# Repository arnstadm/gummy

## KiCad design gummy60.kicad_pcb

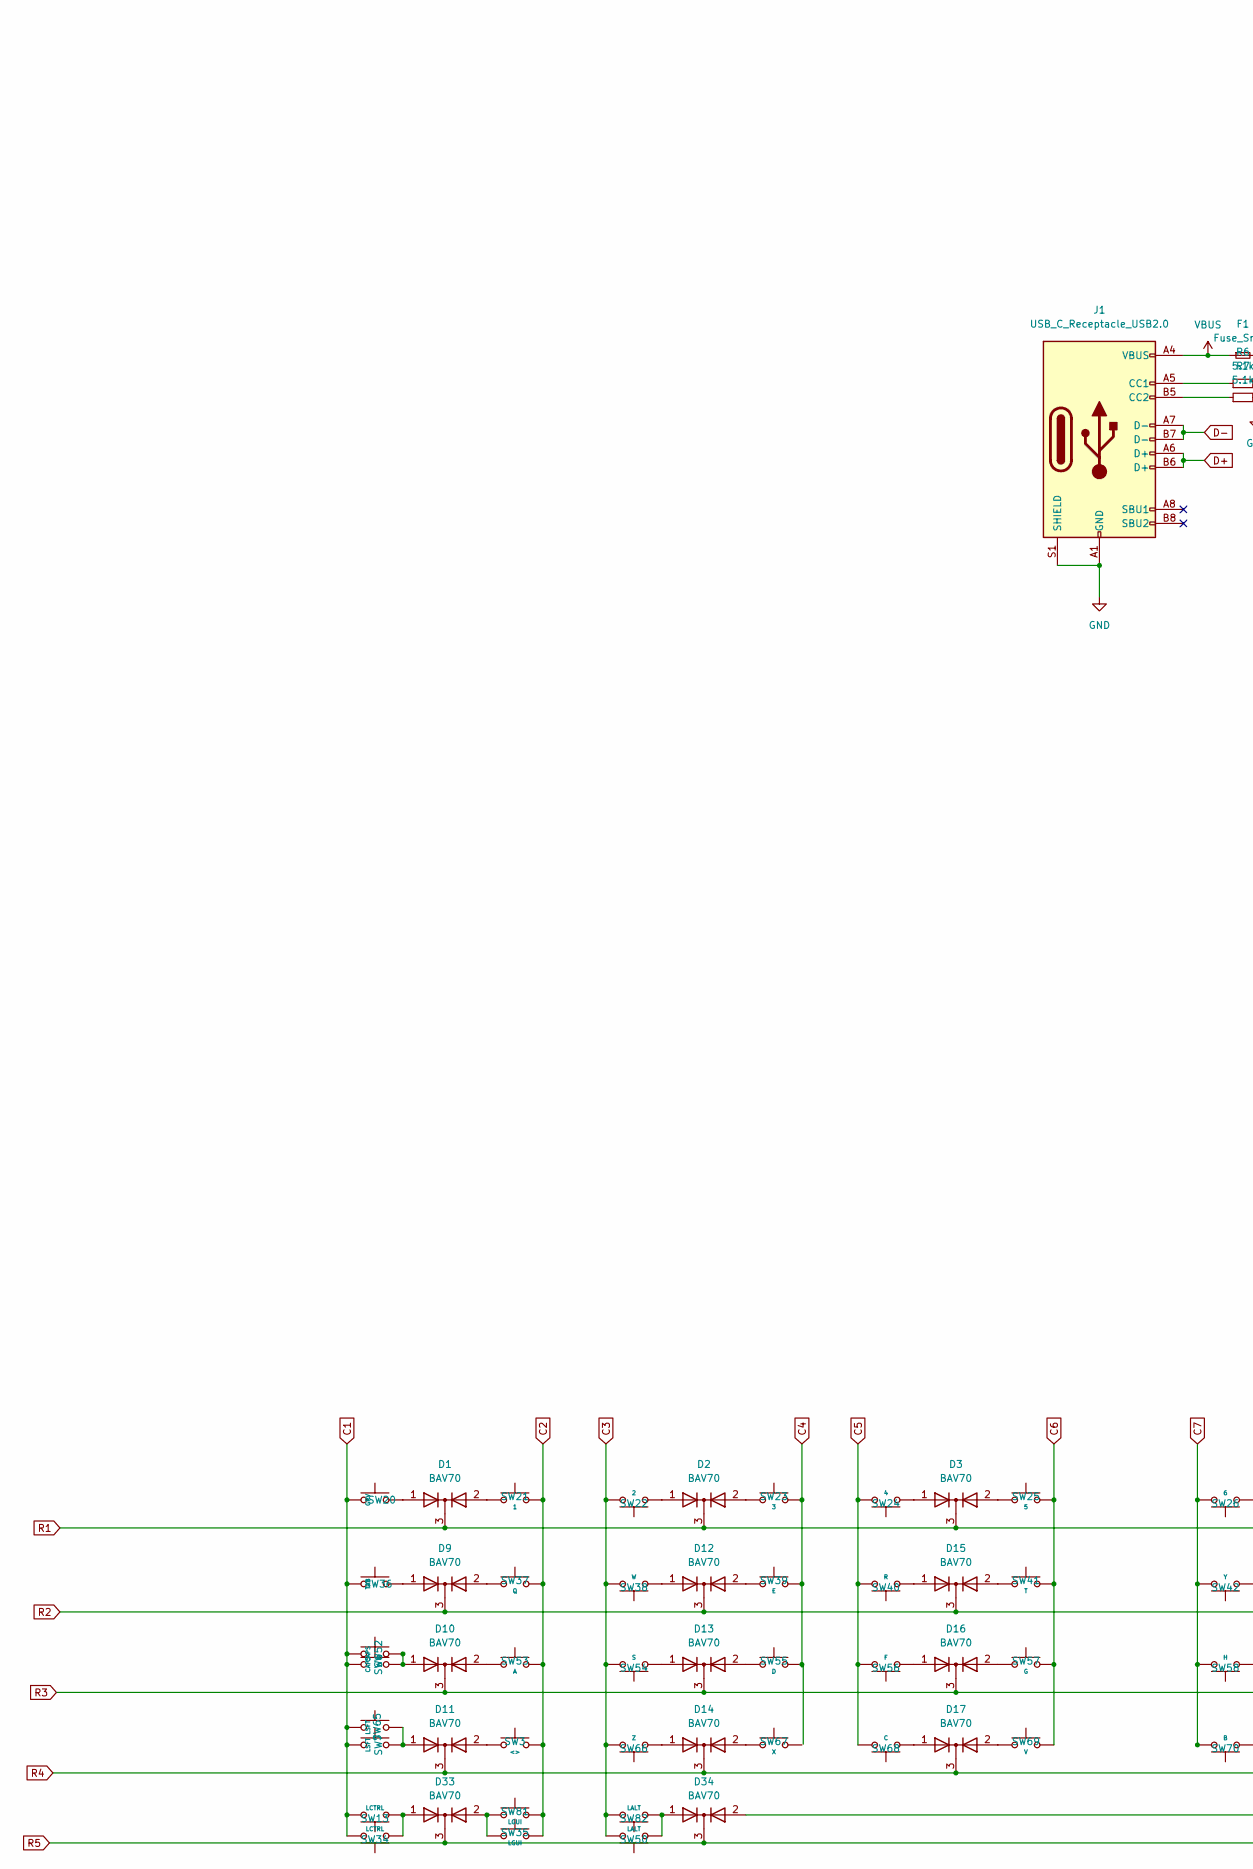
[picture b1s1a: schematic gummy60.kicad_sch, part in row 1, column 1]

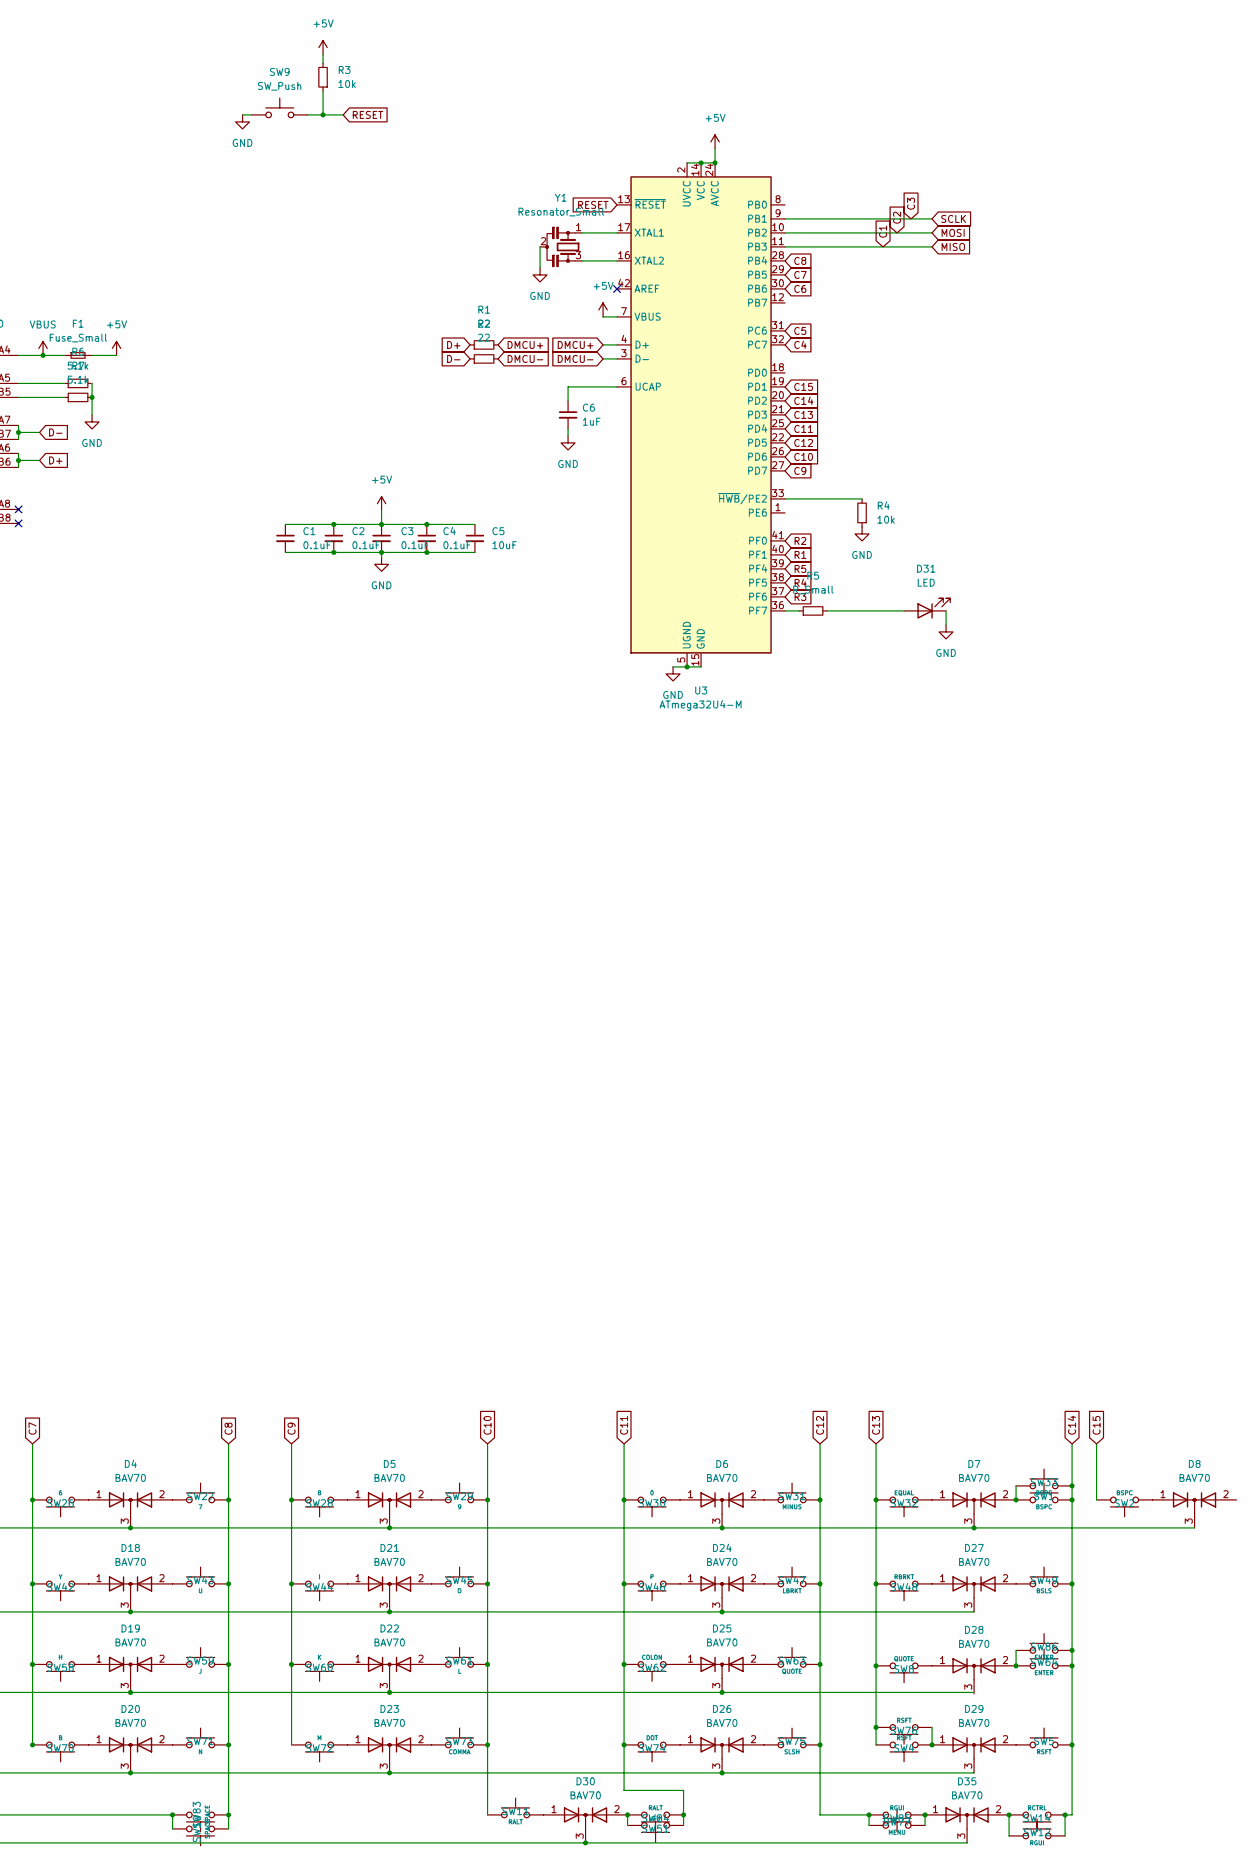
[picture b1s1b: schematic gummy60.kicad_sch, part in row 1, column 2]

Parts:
C1, C2, C3, C4: 0.1uF; C_0603_1608Metric
C5: 10uF; C_0603_1608Metric
C6: 1uF; C_0603_1608Metric
D1, D2, D3, D4, D5, D6, D7, D8, D9, D10, D11, D12, D13, D14, D15, D16, D17, D18, D19, D20, D21, D22, D23, D24, D25, D26, D27, D28, D29, D30, D33, D34, D35: BAV70; SOT-23
D31: LED
F1: Fuse_Small; Fuse_0603_1608Metric
J1: USB_C_Receptacle_USB2.0; USB_C_Receptacle_HRO_TYPE-C-31-M-12
R1, R2: 22; R_0603_1608Metric
R3, R4: 10k; R_0603_1608Metric
R5: R_Small; R_0603_1608Metric
R6, R7: 5.1k; R_0603_1608Metric
SW1, SW2, SW3, SW5, SW8, SW20, SW21, SW22, SW23, SW24, SW25, SW26, SW27, SW28, SW29, SW30, SW31, SW32, SW37, SW38, SW39, SW40, SW41, SW42, SW43, SW44, SW45, SW46, SW47, SW48, SW53, SW54, SW55, SW56, SW57, SW58, SW59, SW60, SW61, SW62, SW63, SW66, SW67, SW68, SW69, SW70, SW71, SW72, SW73, SW74, SW75, SW81, SW85: CPG151101S11; MXOnly-1U-NoLED
SW4: CPG151101S11; MXOnly-1.75U-NoLED
SW6: CPG151101S11; MXOnly-1.25U
SW7, SW11, SW12, SW34, SW35, SW50, SW51, SW77: CPG151101S11; MXOnly-1.25U-NoLED
SW9: SW_Push; SKQG-1155865
SW10: CPG151101S11; MXOnly-6.25U-ReversedStabilizers-NoLED
SW13, SW14, SW36, SW49, SW82, SW84: CPG151101S11; MXOnly-1.5U-NoLED
SW33: CPG151101S11; MXOnly-2U-NoLED
SW52: CPG151101S11; MXOnly-1.75U
SW64: CPG151101S11; MXOnly-2.25U-ReversedStabilizers-NoLED
SW65: CPG151101S11; MXOnly-2.25U-NoLED
SW76: CPG151101S11; MXOnly-2.75U-NoLED
SW83: CPG151101S11; MXOnly-7U-ReversedStabilizers-NoLED
SW86: CPG151101S11; MXOnly-ISO-ReversedStabilizers
U3: ATmega32U4-M; QFN-44-1EP_7x7mm_P0.5mm_EP5.2x5.2mm
Y1: Resonator_Small; Resonator_SMD_Murata_CSTxExxV-3Pin_3.0x1.1mm

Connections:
+5V: C1.1, C2.1, C3.1, C4.1, C5.1, F1.2, R3.2, U3.2 (UVCC), U3.7 (VBUS), U3.14 (VCC), U3.24 (AVCC), U3.34 (VCC), U3.44 (AVCC)
C1: SW6.2, SW7.2, SW13.2, SW20.2, SW34.2, SW36.2, SW52.2, SW65.2, U3.11 (PB3)
C2: SW3.2, SW21.2, SW35.2, SW37.2, SW53.2, SW81.2, U3.10 (PB2)
C3: SW22.2, SW38.2, SW50.2, SW54.2, SW66.2, SW82.2, U3.9 (PB1)
C4: SW23.2, SW39.2, SW55.2, U3.32 (PC7)
C5: SW24.2, SW40.2, SW56.2, SW68.2, U3.31 (PC6)
C6: SW25.2, SW41.2, SW57.2, SW69.2, U3.30 (PB6)
C7: SW26.2, SW42.2, SW58.2, SW70.2, U3.29 (PB5)
C8: SW10.2, SW27.2, SW43.2, SW59.2, SW71.2, SW83.2, U3.28 (PB4)
C9: SW28.2, SW44.2, SW60.2, SW72.2, U3.27 (PD7)
C10: SW11.2, SW29.2, SW45.2, SW61.2, SW73.2, U3.26 (PD6)
C11: SW30.2, SW46.2, SW51.2, SW62.2, SW74.2, SW84.2, U3.25 (PD4)
C12: SW31.2, SW47.2, SW63.2, SW75.2, SW77.2, SW85.2, U3.22 (PD5)
C13: SW4.2, SW8.2, SW32.2, SW48.2, SW76.2, U3.21 (PD3)
C14: SW1.2, SW5.2, SW12.2, SW14.2, SW33.2, SW49.2, SW64.2, SW86.2, U3.20 (PD2)
C15: SW2.2, U3.19 (PD1)
D+: J1.A6 (D+), J1.B6 (D+), R1.1
D-: J1.A7 (D-), J1.B7 (D-), R2.1
DMCU+: R1.2, U3.4 (D+)
DMCU-: R2.2, U3.3 (D-)
GND: C1.2, C2.2, C3.2, C4.2, C5.2, C6.2, D31.1 (K), J1.A1 (GND), J1.A12 (GND), J1.B1 (GND), J1.B12 (GND), J1.S1 (SHIELD), R4.1, R6.2, R7.2, SW9.1, U3.5 (UGND), U3.15 (GND), U3.23 (GND), U3.35 (GND), U3.43 (GND), U3.45 (GND), Y1.2
unnamed: C6.1, U3.6 (UCAP)
unnamed: D1.1 (A), SW20.1
unnamed: D1.2 (A), SW21.1
unnamed: D2.1 (A), SW22.1
unnamed: D2.2 (A), SW23.1
unnamed: D3.1 (A), SW24.1
unnamed: D3.2 (A), SW25.1
unnamed: D4.1 (A), SW26.1
unnamed: D4.2 (A), SW27.1
unnamed: D5.1 (A), SW28.1
unnamed: D5.2 (A), SW29.1
unnamed: D6.1 (A), SW30.1
unnamed: D6.2 (A), SW31.1
unnamed: D7.1 (A), SW32.1
unnamed: D7.2 (A), SW1.1, SW33.1
unnamed: D8.1 (A), SW2.1
unnamed: D9.1 (A), SW36.1
unnamed: D9.2 (A), SW37.1
unnamed: D10.1 (A), SW6.1, SW52.1
unnamed: D10.2 (A), SW53.1
unnamed: D11.1 (A), SW7.1, SW65.1
unnamed: D11.2 (A), SW3.1
unnamed: D12.1 (A), SW38.1
unnamed: D12.2 (A), SW39.1
unnamed: D13.1 (A), SW54.1
unnamed: D13.2 (A), SW55.1
unnamed: D14.1 (A), SW66.1
unnamed: D14.2 (A), SW67.1
unnamed: D15.1 (A), SW40.1
unnamed: D15.2 (A), SW41.1
unnamed: D16.1 (A), SW56.1
unnamed: D16.2 (A), SW57.1
unnamed: D17.1 (A), SW68.1
unnamed: D17.2 (A), SW69.1
unnamed: D18.1 (A), SW42.1
unnamed: D18.2 (A), SW43.1
unnamed: D19.1 (A), SW58.1
unnamed: D19.2 (A), SW59.1
unnamed: D20.1 (A), SW70.1
unnamed: D20.2 (A), SW71.1
unnamed: D21.1 (A), SW44.1
unnamed: D21.2 (A), SW45.1
unnamed: D22.1 (A), SW60.1
unnamed: D22.2 (A), SW61.1
unnamed: D23.1 (A), SW72.1
unnamed: D23.2 (A), SW73.1
unnamed: D24.1 (A), SW46.1
unnamed: D24.2 (A), SW47.1
unnamed: D25.1 (A), SW62.1
unnamed: D25.2 (A), SW63.1
unnamed: D26.1 (A), SW74.1
unnamed: D26.2 (A), SW75.1
unnamed: D27.1 (A), SW48.1
unnamed: D27.2 (A), SW49.1
unnamed: D28.1 (A), SW8.1
unnamed: D28.2 (A), SW64.1, SW86.1
unnamed: D29.1 (A), SW4.1, SW76.1
unnamed: D29.2 (A), SW5.1
unnamed: D30.1 (A), SW11.1
unnamed: D30.2 (A), SW51.1, SW84.1
unnamed: D31.2 (A), R5.2
unnamed: D33.1 (A), SW13.1, SW34.1
unnamed: D33.2 (A), SW35.1, SW81.1
unnamed: D34.1 (A), SW50.1, SW82.1
unnamed: D34.2 (A), SW10.1, SW83.1
unnamed: D35.1 (A), SW77.1, SW85.1
unnamed: D35.2 (A), SW12.1, SW14.1
unnamed: J1.A5 (CC1), R6.1
unnamed: J1.B5 (CC2), R7.1
unnamed: R4.2, U3.33 (~HWB/PE2)
unnamed: R5.1, U3.36 (PF7)
unnamed: U3.16 (XTAL2), Y1.3
unnamed: U3.17 (XTAL1), Y1.1
R1: D1.3 (K), D2.3 (K), D3.3 (K), D4.3 (K), D5.3 (K), D6.3 (K), D7.3 (K), D8.3 (K), U3.40 (PF1)
R2: D9.3 (K), D12.3 (K), D15.3 (K), D18.3 (K), D21.3 (K), D24.3 (K), D27.3 (K), U3.41 (PF0)
R3: D10.3 (K), D13.3 (K), D16.3 (K), D19.3 (K), D22.3 (K), D25.3 (K), U3.37 (PF6)
R4: D11.3 (K), D14.3 (K), D17.3 (K), D20.3 (K), D23.3 (K), D26.3 (K), D29.3 (K), U3.38 (PF5)
R5: D30.3 (K), D33.3 (K), D34.3 (K), D35.3 (K), U3.39 (PF4)
RESET: R3.1, SW9.2, U3.13 (~RESET)
VBUS: F1.1, J1.A4 (VBUS), J1.A9 (VBUS), J1.B4 (VBUS), J1.B9 (VBUS)

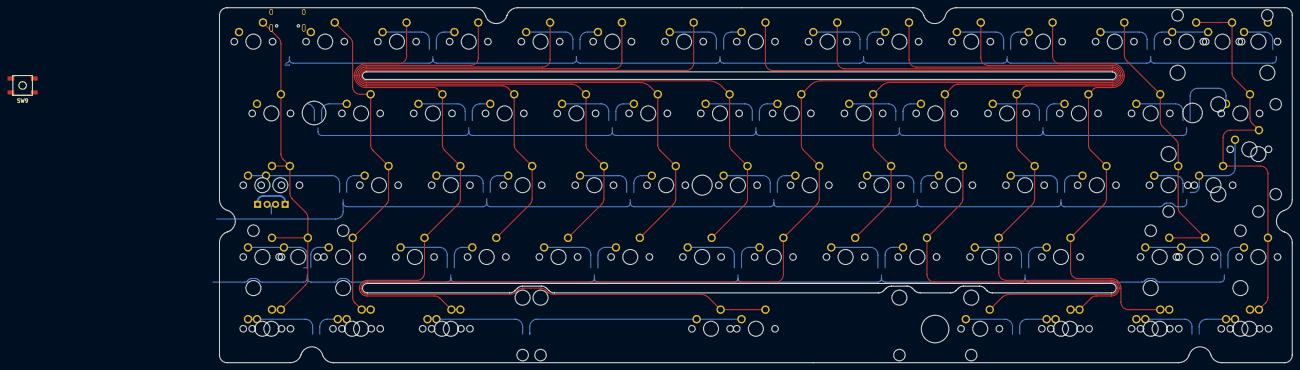
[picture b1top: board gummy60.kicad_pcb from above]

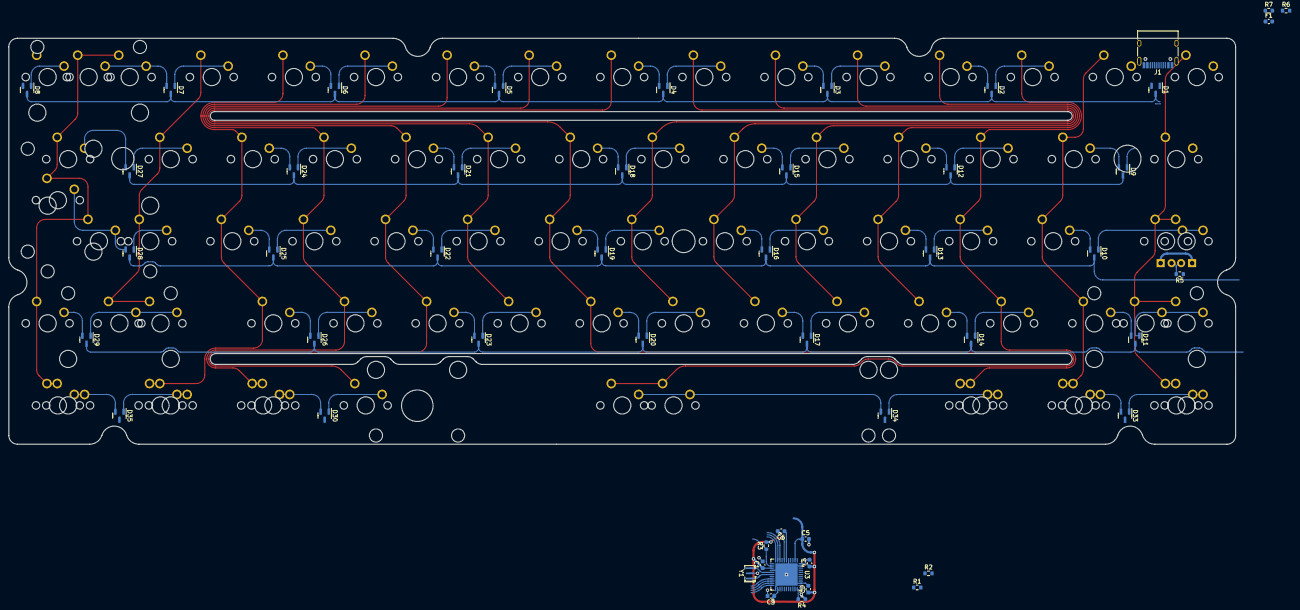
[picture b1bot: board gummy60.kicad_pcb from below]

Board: 2 copper layers, 284.7 x 94.2 mm, 128 parts (50 on the bottom side), 100 nets.

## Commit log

2022-01-02 Properly placed usb
